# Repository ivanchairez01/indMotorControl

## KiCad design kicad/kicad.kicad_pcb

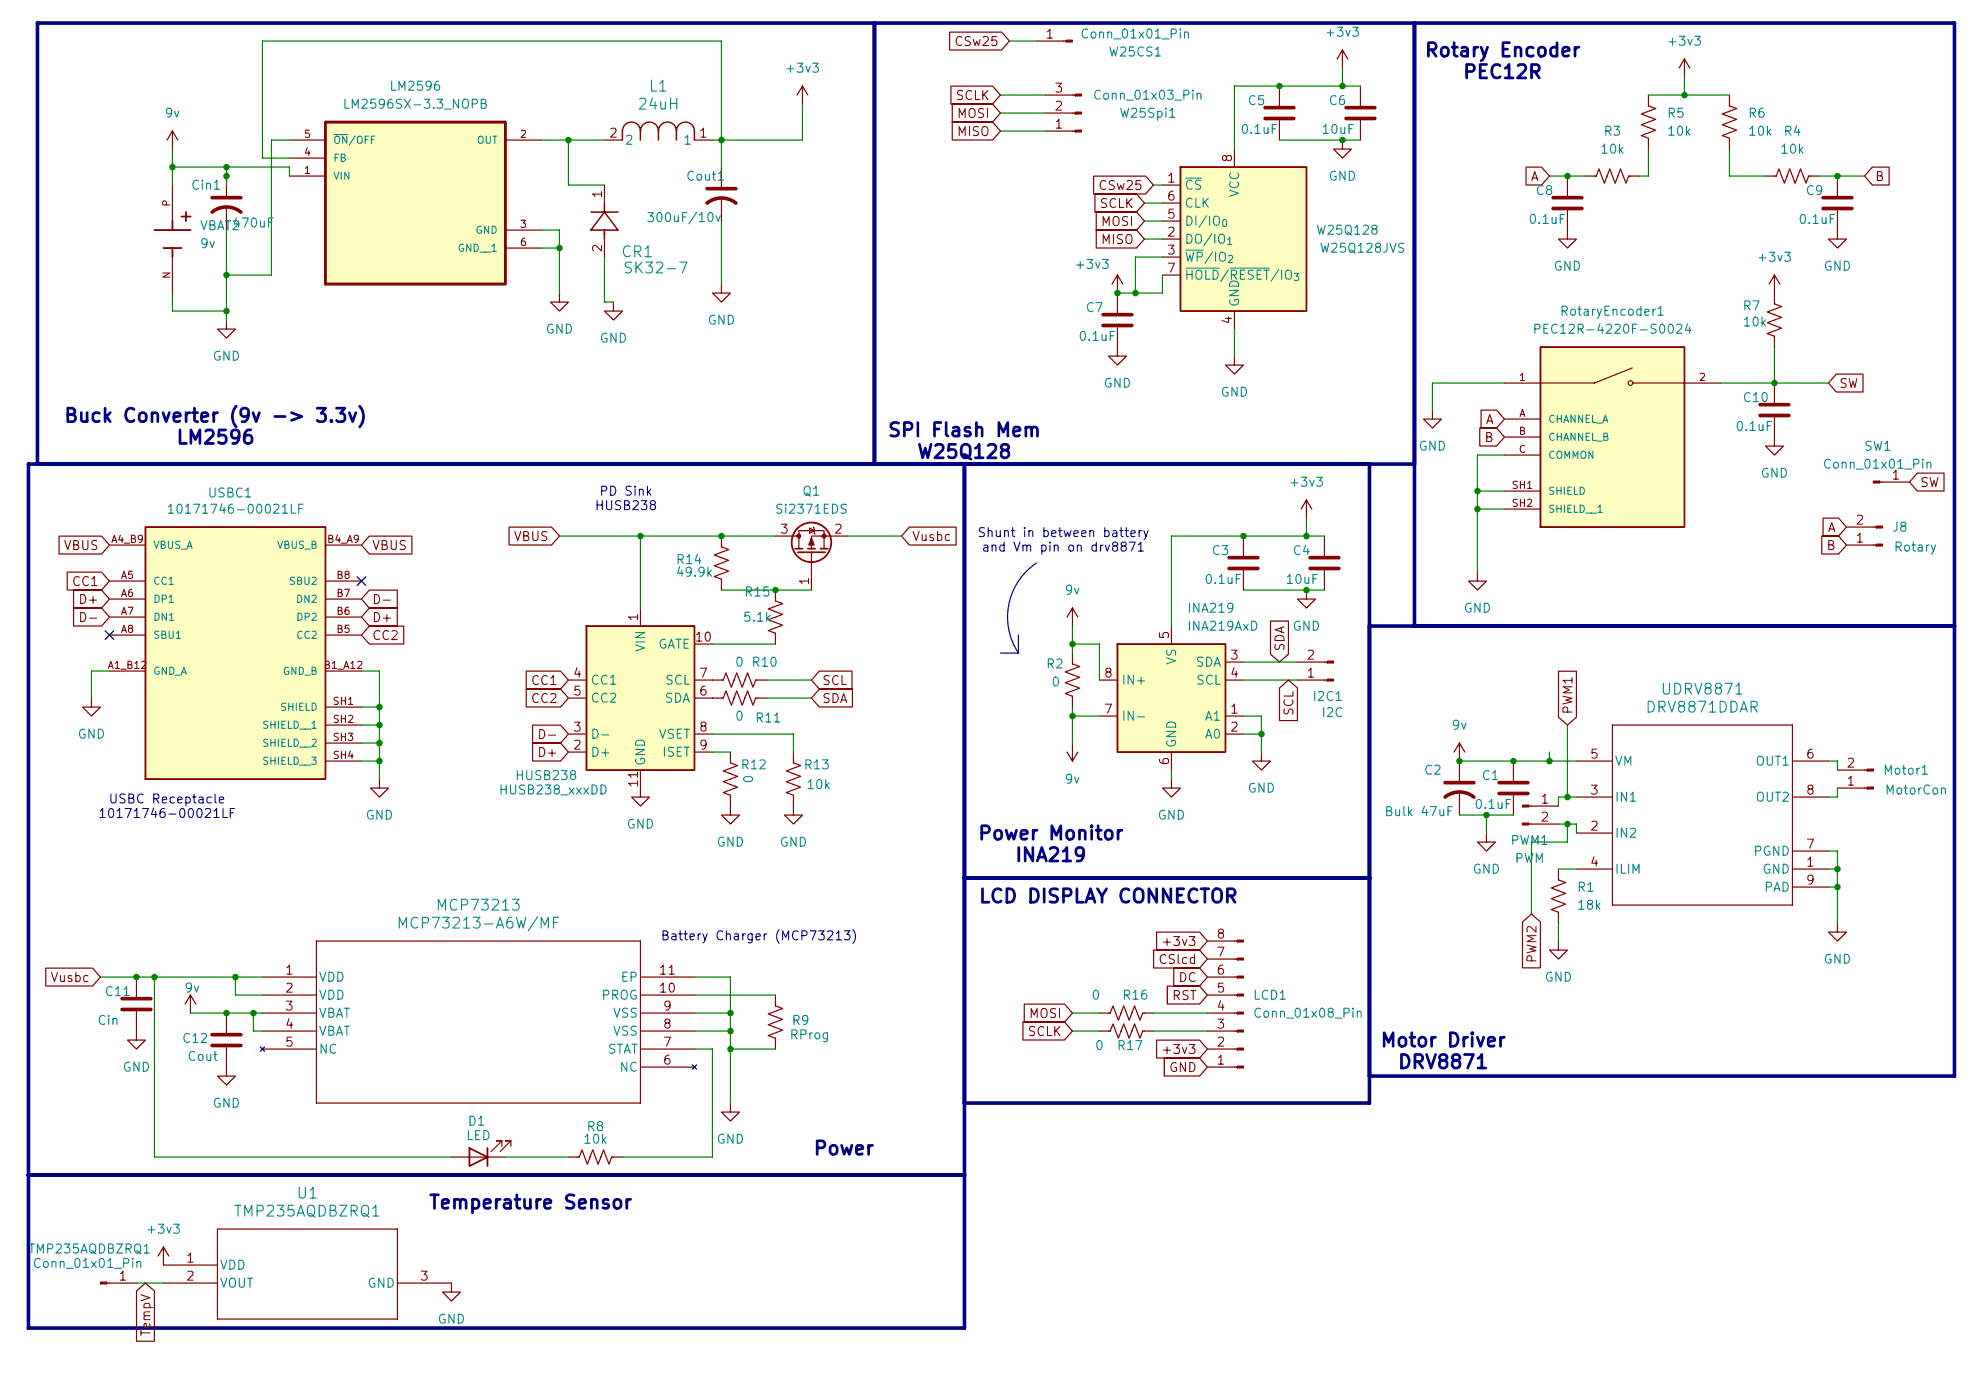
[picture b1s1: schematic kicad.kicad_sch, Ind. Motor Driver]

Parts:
C1, C3, C5, C7, C8, C9, C10: 0.1uF; C_0805_2012Metric
C2: Bulk 47uF; CP_Elec_6.3x5.8
C4, C6: 10uF; C_0805_2012Metric
C11: Cin; C_0805_2012Metric
C12: Cout; C_0805_2012Metric
CR1: SK32-7; SMC_DIO-M
Cin1: 470uF; CP_Elec_6.3x5.8
Cout1: 300uF/10v; CP_Elec_6.3x5.8
D1: LED; LED_0805_2012Metric_Pad1.15x1.40mm_HandSolder
HUSB238: HUSB238_xxxDD; WDFN-10-1EP_3x3mm_P0.5mm_EP1.8x2.5mm
I2C1: I2C; PinHeader_1x02_P2.54mm_Vertical
INA219: INA219AxD; SOIC-8_3.9x4.9mm_P1.27mm
J8: Rotary; PinHeader_1x02_P2.54mm_Vertical
L1: 24uH; IND_LCI-44_PE-53932_PUL
LCD1: Conn_01x08_Pin; PinHeader_1x08_P2.54mm_Vertical
LM2596: LM2596SX-3.3_NOPB; VREG_LM2596SX-3.3_NOPB
MCP73213: MCP73213-A6W/MF; DFN10_3x3MC_MCH
Motor1: MotorCon; PinHeader_1x02_P2.54mm_Vertical
PWM1: PWM; PinHeader_1x02_P2.54mm_Vertical
Q1: Si2371EDS; SOT-23
R1: 18k; R_0805_2012Metric
R2, R10, R11, R12, R16, R17: 0; R_0805_2012Metric
R3, R4, R5, R6, R7, R8, R13: 10k; R_0805_2012Metric
R9: RProg; R_0805_2012Metric
R14: 49.9k; R_0805_2012Metric
R15: 5.1k; R_0805_2012Metric
RotaryEncoder1: PEC12R-4220F-S0024; XDCR_PEC12R-4220F-S0024; PARTREV 07/21
SW1: Conn_01x01_Pin; PinHeader_1x01_P2.54mm_Vertical
TMP235AQDBZRQ1: Conn_01x01_Pin; PinHeader_1x01_P2.54mm_Vertical
U1: TMP235AQDBZRQ1; SOT_AQDBZRQ1_TEX
UDRV8871: DRV8871DDAR; DDA0008H_M
USBC1: 10171746-00021LF; AMPHENOL_10171746-00021LF; PARTREV A
VBAT2: 9v; BAT_1294; PARTREV C
W25CS1: Conn_01x01_Pin; PinHeader_1x01_P2.54mm_Vertical
W25Q128: W25Q128JVS; SOIC-8_5.3x5.3mm_P1.27mm
W25Spi1: Conn_01x03_Pin; PinHeader_1x03_P2.54mm_Vertical

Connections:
9v: C1.1, C2.1, C12.1, Cin1.1, INA219.7 (IN-), INA219.8 (IN+), LM2596.1 (VIN), MCP73213.3 (VBAT), MCP73213.4 (VBAT), R2.1, R2.2, UDRV8871.5 (VM), VBAT2.P
+3v3: C3.1, C4.1, C5.1, C6.1, C7.1, Cout1.1, INA219.5 (VS), L1.1, LCD1.2, LCD1.8, LM2596.4 (FB), R5.1, R6.1, R7.1, U1.1 (VDD), W25Q128.3 (~WP/IO_{2}), W25Q128.7 (~HOLD/~RESET/IO_{3}), W25Q128.8 (VCC); also elsewhere on the board
A: C8.1, J8.2, R3.1, RotaryEncoder1.A (CHANNEL_A)
B: C9.1, J8.1, R4.2, RotaryEncoder1.B (CHANNEL_B)
CC1: HUSB238.4 (CC1), USBC1.A5 (CC1)
CC2: HUSB238.5 (CC2), USBC1.B5 (CC2)
CSlcd: LCD1.7
CSw25: W25CS1.1 (Pin_1_1), W25Q128.1 (~CS)
D+: HUSB238.2 (D+), USBC1.A6 (DP1), USBC1.B6 (DP2)
D-: HUSB238.3 (D-), USBC1.A7 (DN1), USBC1.B7 (DN2)
DC: LCD1.6
GND: C1.2, C2.2, C3.2, C4.2, C5.2, C6.2, C7.2, C8.2, C9.2, C10.2, C11.2, C12.2, CR1.2, Cin1.2, Cout1.2, HUSB238.11 (GND), INA219.1 (A1), INA219.2 (A0), INA219.6 (GND), LCD1.1, LM2596.3 (GND), LM2596.5 (~ON/OFF), LM2596.6 (GND__1), MCP73213.8 (VSS), MCP73213.9 (VSS), MCP73213.11 (EP), R1.2, R9.1, R12.2, R13.2, RotaryEncoder1.1, RotaryEncoder1.C (COMMON), RotaryEncoder1.SH1 (SHIELD), RotaryEncoder1.SH2 (SHIELD__1), U1.3 (GND), UDRV8871.1 (GND), UDRV8871.7 (PGND), UDRV8871.9 (PAD), USBC1.A1_B12 (GND_A), USBC1.B1_A12 (GND_B), USBC1.SH1 (SHIELD), USBC1.SH2 (SHIELD__1), USBC1.SH3 (SHIELD__2), USBC1.SH4 (SHIELD__3), VBAT2.N, W25Q128.4 (GND); also elsewhere on the board
MISO: W25Q128.2 (DO/IO_{1}), W25Spi1.1
MOSI: R16.1, W25Q128.5 (DI/IO_{0}), W25Spi1.2
unnamed: D1.1 (K), R8.2
unnamed: HUSB238.10 (GATE), R15.2
unnamed: HUSB238.9 (ISET), R12.1
unnamed: HUSB238.7 (SCL), R10.2
unnamed: HUSB238.6 (SDA), R11.2
unnamed: HUSB238.8 (VSET), R13.1
unnamed: LCD1.3, R17.2
unnamed: LCD1.4, R16.2
unnamed: CR1.1, L1.2, LM2596.2 (OUT)
unnamed: MCP73213.10 (PROG), R9.2
unnamed: MCP73213.7 (STAT), R8.1
unnamed: Motor1.1, UDRV8871.8 (OUT2)
unnamed: Motor1.2, UDRV8871.6 (OUT1)
unnamed: Q1.1 (G), R14.2, R15.1
unnamed: R3.2, R5.2
unnamed: R4.1, R6.2
unnamed: R1.1, UDRV8871.4 (ILIM)
PWM1: PWM1.1, UDRV8871.3 (IN1)
PWM2: PWM1.2, UDRV8871.2 (IN2)
RST: LCD1.5
SCL: I2C1.1, INA219.4 (SCL), R10.1
SCLK: R17.1, W25Q128.6 (CLK), W25Spi1.3
SDA: I2C1.2, INA219.3 (SDA), R11.1
SW: C10.1, R7.2, RotaryEncoder1.2, SW1.1 (Pin_1_1)
TempV: TMP235AQDBZRQ1.1 (Pin_1_1), U1.2 (VOUT); also elsewhere on the board
VBUS: HUSB238.1 (VIN), Q1.3 (D), R14.1, USBC1.A4_B9 (VBUS_A), USBC1.B4_A9 (VBUS_B)
Vusbc: C11.1, D1.2 (A), MCP73213.1 (VDD), MCP73213.2 (VDD), Q1.2 (S)

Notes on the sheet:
Temperature Sensor
Shunt in between battery and Vm pin on drv8871
SPI Flash Mem W25Q128
LCD DISPLAY CONNECTOR
Battery Charger (MCP73213)
Rotary Encoder PEC12R
Motor Driver DRV8871
Power Monitor INA219
Buck Converter (9v -> 3.3v) LM2596
USBC Receptacle 10171746-00021LF
Power
PD Sink HUSB238

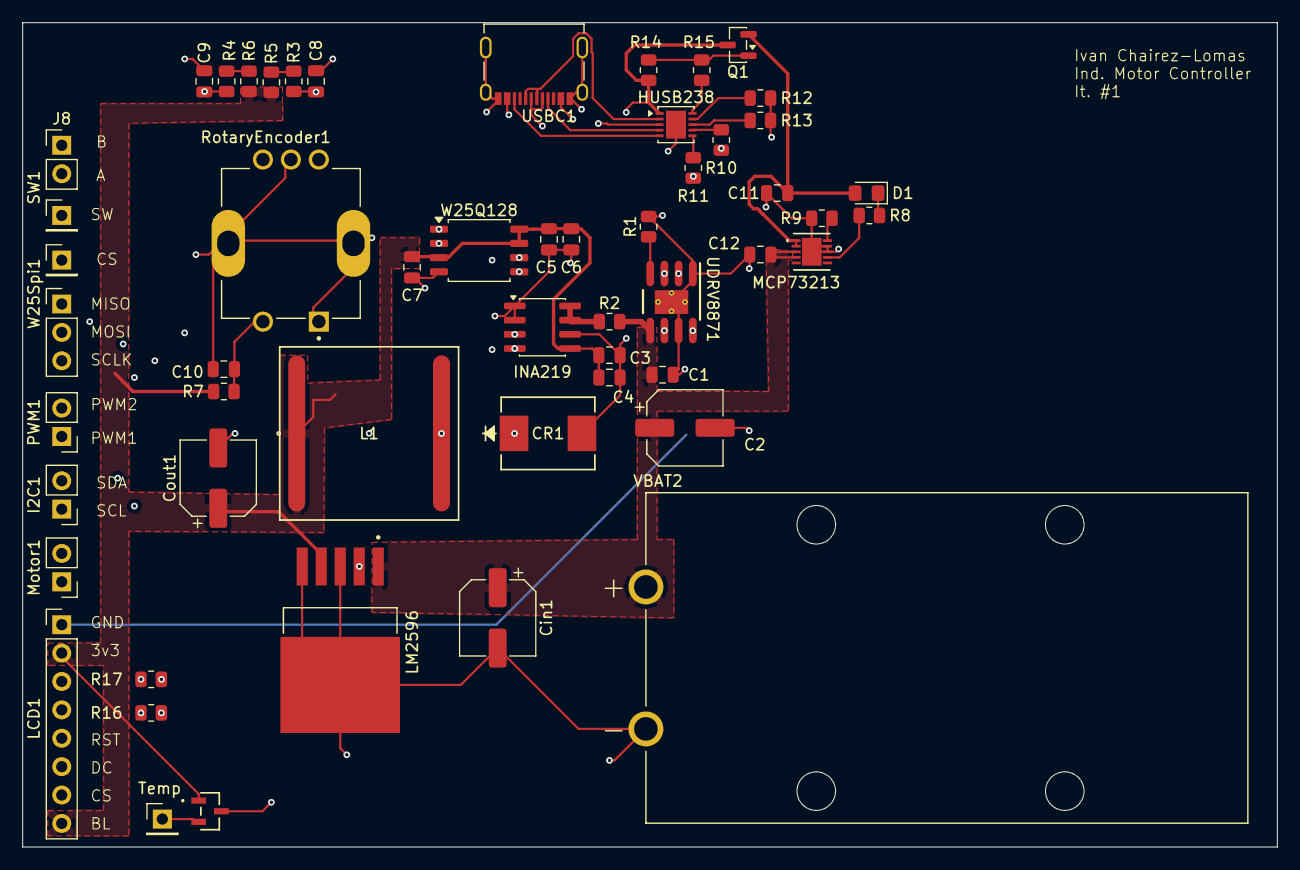
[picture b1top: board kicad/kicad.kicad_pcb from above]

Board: 4 copper layers, 112.2 x 73.8 mm, 54 parts (0 on the bottom side), 38 nets.

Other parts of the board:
Temp: TMP235AQDBZRQ1; SOT_AQDBZRQ1_TEX

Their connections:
+3v3: Temp.1 (VDD); also elsewhere on the board
GND: Temp.3 (GND); also elsewhere on the board
TempV: Temp.2 (VOUT); also elsewhere on the board

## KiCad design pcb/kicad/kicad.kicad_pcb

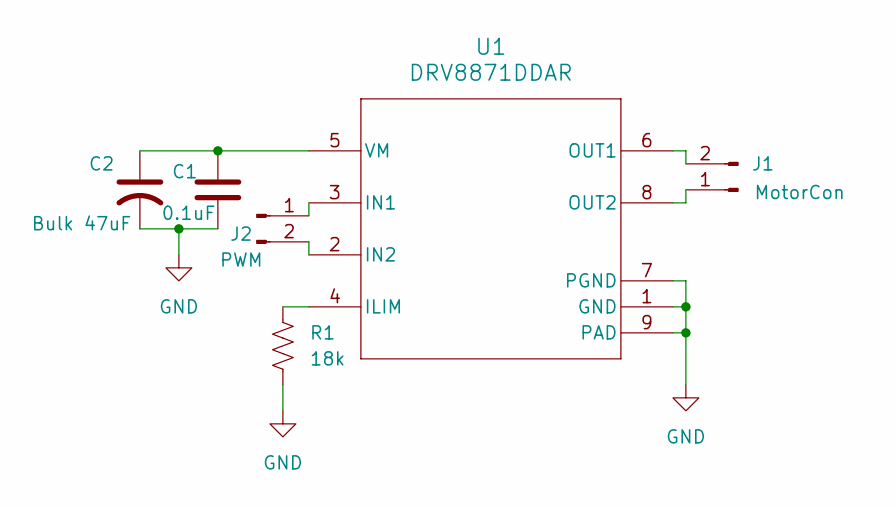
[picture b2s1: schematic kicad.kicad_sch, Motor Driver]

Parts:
C1: 0.1uF; C_0805_2012Metric
C2: Bulk 47uF; CP_Elec_6.3x5.8
J1: MotorCon; PinHeader_1x02_P2.54mm_Vertical
J2: PWM; PinHeader_1x02_P2.54mm_Vertical
R1: 18k; R_0805_2012Metric
U1: DRV8871DDAR; DDA0008H_M

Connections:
GND: C1.2, C2.2, R1.2, U1.1 (GND), U1.7 (PGND), U1.9 (PAD)
unnamed: J1.1, U1.8 (OUT2)
unnamed: J1.2, U1.6 (OUT1)
unnamed: J2.1, U1.3 (IN1)
unnamed: J2.2, U1.2 (IN2)
unnamed: R1.1, U1.4 (ILIM)
unnamed: C1.1, C2.1, U1.5 (VM)

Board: 4 copper layers, 6 parts (0 on the bottom side), 7 nets, no tracks yet.

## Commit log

2026-06-08 Project Description
2026-06-11 Motor Driver Hardware
2026-06-15 power pcb
2026-06-30 LCD display UI pictures
2026-06-30 edited lcd option boxes
